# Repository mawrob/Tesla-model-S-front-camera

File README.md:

# Tesla-model-S-front-camera
Module to enable switching between a newly added front camera and the standard rear camera.

These are the camera switch manufacturing files for a Tesla Model S.

See: http://www.teslarati.com/tesla-model-s-front-camera-touchscreen-kit/

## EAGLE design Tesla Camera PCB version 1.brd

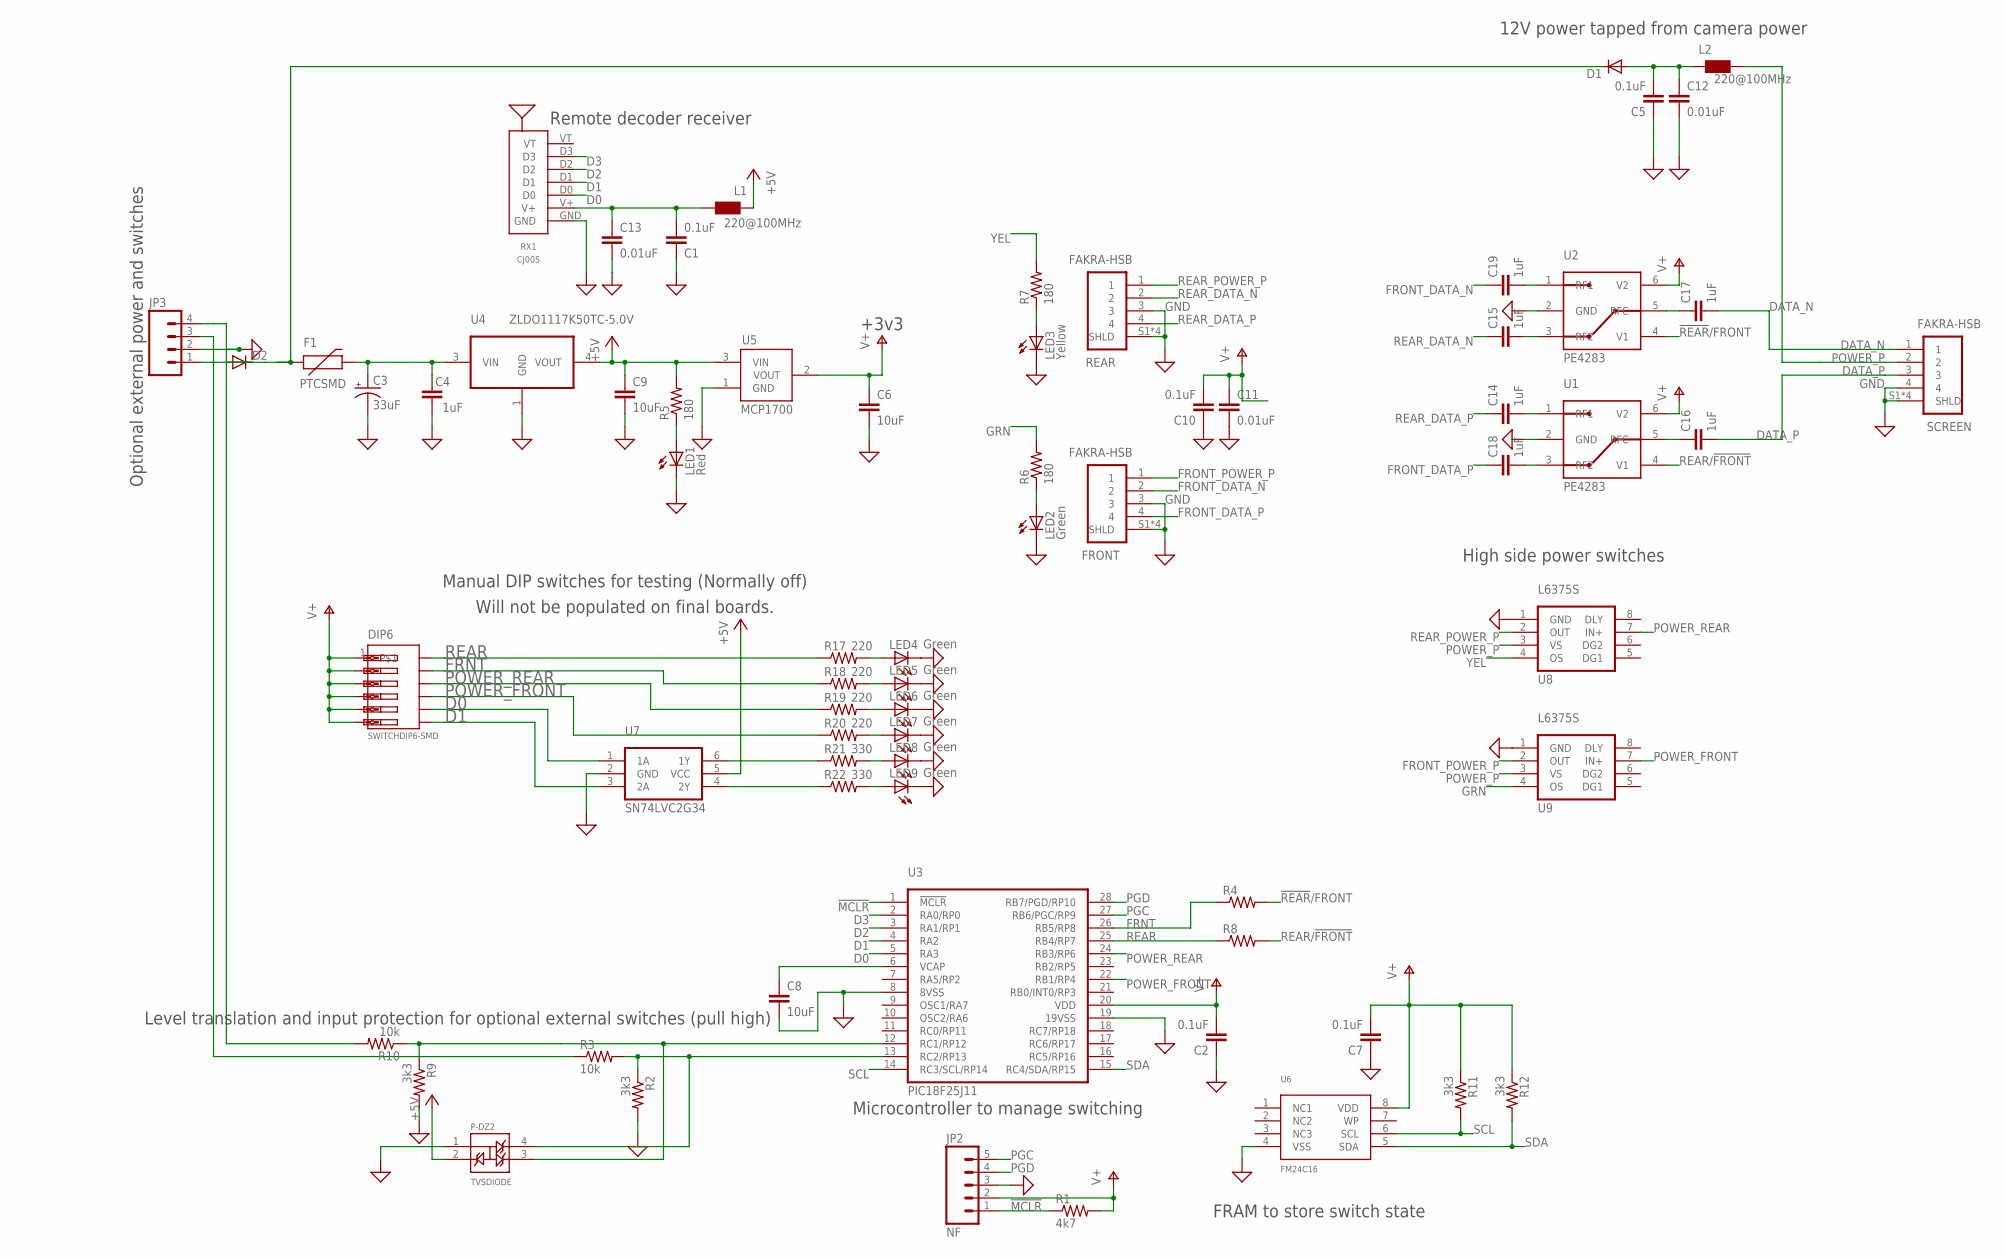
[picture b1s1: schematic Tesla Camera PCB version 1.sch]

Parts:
C1, C2, C5, C7, C10: 0.1uF; 0805
C3: 33uF; CAPVTYPE
C4: 1uF; 0805
C6, C8, C9: 10uF; 0805
C11, C12, C13: 0.01uF; 0805
C14, C15, C16, C17, C18, C19: 1uF; 0603-CAP
D1, D2: DIODE-DO-214AC; DO-214AC
DIP6: SWITCHDIP6-SMD; SWITCHDIP6
F1: PTCSMD; PTC-1206
FRONT: FAKRA-HSB; FAKRA
JP2: NF; 1X05_LOCK
JP3: M04-LOCK; 1X04_TERM_3.5MM
L1, L2: 220@100MHz; 0805
LED1: Red; 0805_LED
LED2, LED4, LED5, LED6, LED7, LED8, LED9: Green; 0805_LED
LED3: Yellow; 0805_LED
P-DZ2: TVSDIODE; SOT143
R1: 4k7; 0805
R2, R9, R11, R12: 3k3; 0805
R3, R10: 10k; 0805
R4, R8: RESISTOR; 0805
R5, R6, R7: 180; 0805
R17, R18, R19, R20: 220; 0805
R21, R22: 330; 0805
REAR: FAKRA-HSB; FAKRA
RX1: CJ005
SCREEN: FAKRA-HSB; FAKRA
U1, U2: PE4283; SC70-6
U3: PIC18F25J11; SOIC-28-WIDE
U4: ZLDO1117K50TC-5.0V; TO252
U5: MCP1700; SOT23-3
U6: FM24C16; TDFN-8-FRAM
U7: SN74LVC2G34; SOT23-6
U8, U9: L6375S; SO08-EIAJ

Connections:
!MCLR: JP2.1, R1.1, U3.1 (!MCLR)
!REAR!/FRONT: R4.2, U2.4 (V1)
+5V: C9.1, L1.1, P-DZ2.2, R5.2, U4.4 (VOUT), U5.3 (VIN), U7.5 (VCC)
D0: DIP6.8, RX1.D0, U3.5 (RA3), U7.1 (1A)
D1: DIP6.7, RX1.D1, U3.4 (RA2), U7.3 (2A)
D2: RX1.D2, U3.3 (RA1/RP1)
D3: RX1.D3, U3.2 (RA0/RP0)
DATA_N: C17.2, SCREEN.1
DATA_P: C16.2, SCREEN.3
FRNT: DIP6.11, R4.1, R18.1, U3.26 (RB5/RP8)
FRONT_DATA_N: C19.1, FRONT.2
FRONT_DATA_P: C18.1, FRONT.4
FRONT_POWER_P: FRONT.1, U9.2 (OUT)
GND: C1.1, C2.1, C3.-, C4.2, C5.1, C6.2, C7.1, C8.2, C9.2, C10.1, C11.2, C12.2, C13.2, FRONT.3, FRONT.S1 (SHLD), FRONT.S2 (SHLD), FRONT.S3 (SHLD), FRONT.S4 (SHLD), JP2.3, JP3.2, LED1.C, LED2.C, LED3.C, LED4.C, LED5.C, LED6.C, LED7.C, LED8.C, LED9.C, P-DZ2.1, R2.2, R9.2, REAR.3, REAR.S1 (SHLD), REAR.S2 (SHLD), REAR.S3 (SHLD), REAR.S4 (SHLD), RX1.GND, SCREEN.4, SCREEN.S1 (SHLD), SCREEN.S2 (SHLD), SCREEN.S3 (SHLD), SCREEN.S4 (SHLD), U1.2 (GND), U2.2 (GND), U3.8 (8VSS), U3.19 (19VSS), U4.1 (GND), U5.1 (GND), U6.4 (VSS), U7.2 (GND), U8.1 (GND), U9.1 (GND)
GRN: R6.2, U9.4 (OS)
unnamed: C5.2, C12.1, D1.A, L2.1
unnamed: P-DZ2.3, R9.1, R10.1, U3.12 (RC1/RP12)
unnamed: LED2.A, R6.1
unnamed: JP3.3, R3.1
unnamed: JP3.4, R10.2
unnamed: C8.1, U3.6 (VCAP)
unnamed: C19.2, U2.1 (RF1)
unnamed: C15.2, U2.3 (RF2)
unnamed: D1.C, D2.C, F1.1
unnamed: C17.1, U2.5 (RFC)
unnamed: D2.A, JP3.1
unnamed: C16.1, U1.5 (RFC)
unnamed: LED3.A, R7.1
unnamed: C3.+, C4.1, F1.2, U4.3 (VIN)
unnamed: LED1.A, R5.1
unnamed: C18.2, U1.3 (RF2)
unnamed: C14.2, U1.1 (RF1)
unnamed: LED4.A, R17.2
unnamed: LED5.A, R18.2
unnamed: LED6.A, R19.2
unnamed: LED7.A, R20.2
unnamed: LED8.A, R21.2
unnamed: LED9.A, R22.2
unnamed: R21.1, U7.6 (1Y)
unnamed: R22.1, U7.4 (2Y)
unnamed: P-DZ2.4, R2.1, R3.2, U3.13 (RC2/RP13)
PGC: JP2.5, U3.27 (RB6/PGC/RP9)
PGD: JP2.4, U3.28 (RB7/PGD/RP10)
POWER_FRONT: DIP6.9, R20.1, U3.22 (RB1/RP4), U9.7 (IN+)
POWER_P: L2.2, SCREEN.2, U8.3 (VS), U9.3 (VS)
POWER_REAR: DIP6.10, R19.1, U3.24 (RB3/RP6), U8.7 (IN+)
REAR: DIP6.12, R8.1, R17.1, U3.25 (RB4/RP7)
REAR/!FRONT: R8.2, U1.4 (V1)
REAR_DATA_N: C15.1, REAR.2
REAR_DATA_P: C14.1, REAR.4
REAR_POWER_P: REAR.1, U8.2 (OUT)
SCL: R11.2, U3.14 (RC3/SCL/RP14), U6.6 (SCL)
SDA: R12.2, U3.15 (RC4/SDA/RP15), U6.5 (SDA)
V+: C2.2, C6.1, C7.2, C10.2, C11.1, DIP6.1, DIP6.2, DIP6.3, DIP6.4, DIP6.5, DIP6.6, JP2.2, R1.2, R11.1, R12.1, U1.6 (V2), U2.6 (V2), U3.20 (VDD), U5.2 (VOUT), U6.8 (VDD)
V+1: C1.2, C13.1, L1.2, RX1.V+
YEL: R7.2, U8.4 (OS)

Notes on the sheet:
High side power switches
Remote decoder receiver
Optional external power and switches
FRAM to store switch state
Microcontroller to manage switching
12V power tapped from camera power
+3v3
Level translation and input protection for optional external switches (pull high)
Manual DIP switches for testing (Normally off)
Will not be populated on final boards.

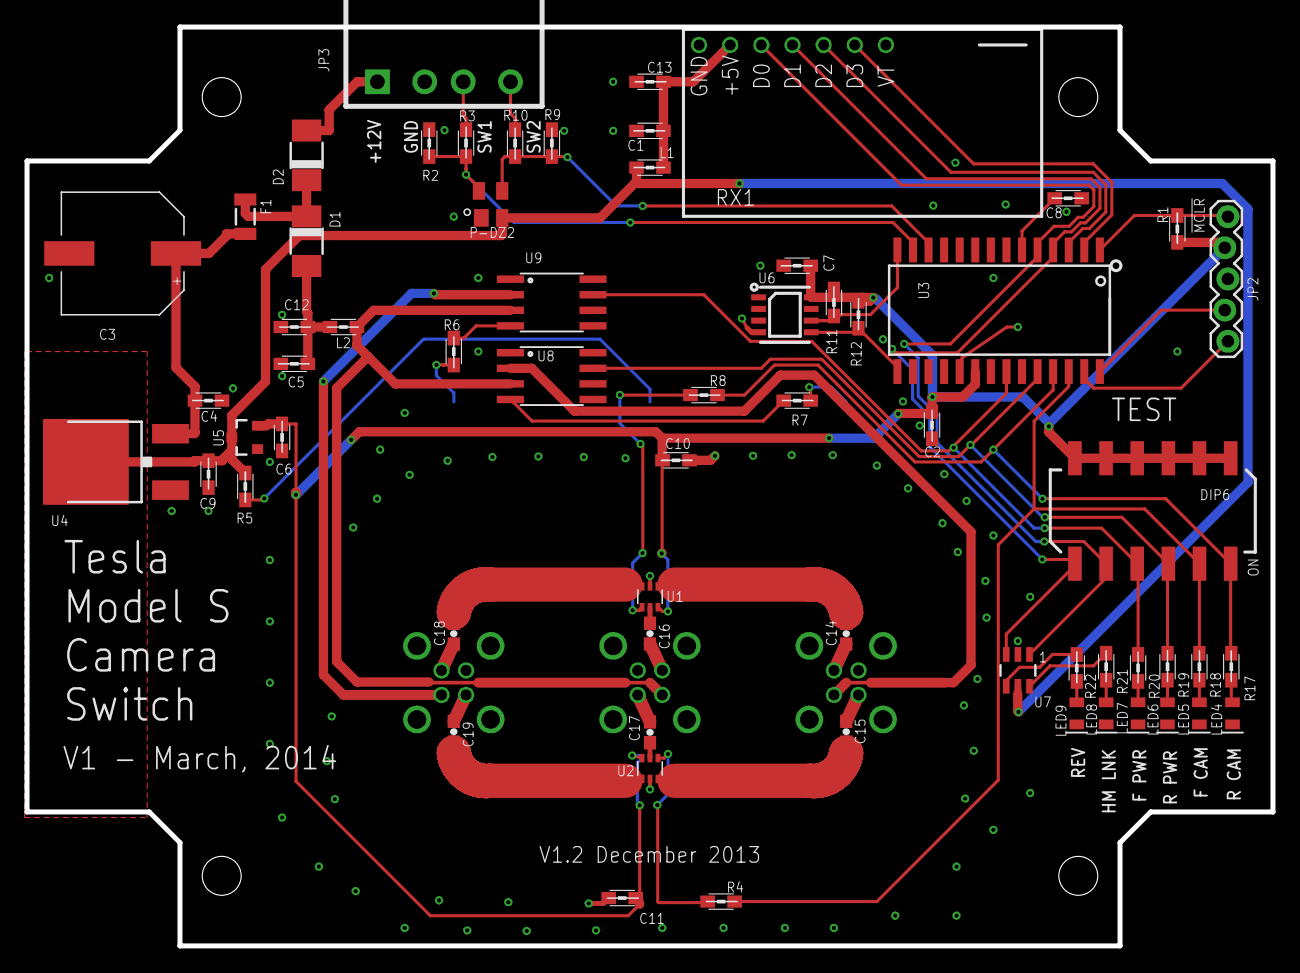
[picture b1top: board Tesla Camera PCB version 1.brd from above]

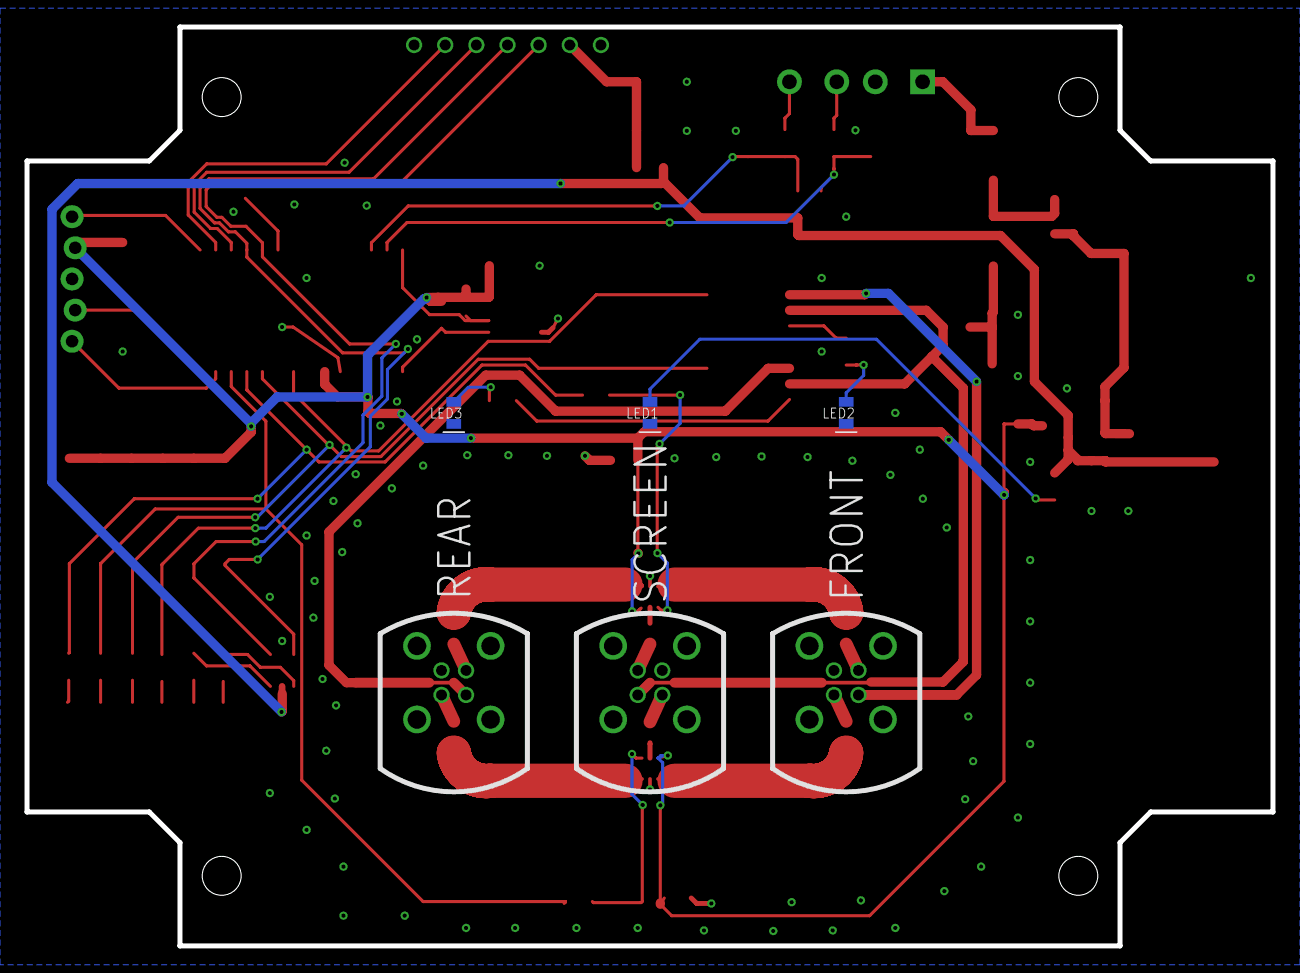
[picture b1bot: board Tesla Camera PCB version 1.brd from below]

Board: 2 copper layers, 101.6 x 74.9 mm, 68 parts (6 on the bottom side), 56 nets.

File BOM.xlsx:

VALUE | DESCRIPTION | MFR | MFPN | VEND | VPN | QTY | EACH | COST | REF | NOTES
33uF | CAP ALUM 33UF 100V 20% SMD | Nichicon | UUX2A330MNL1GS | Digi-Key | 493-6281-1-ND | 1 | 0.33428000000000002 | 0.33428000000000002 | C3 | Alternative Panasonic EEE-HD1J330P
0.1uF | CAP CER 0.1UF 50V 10% X7R 0805 | AVX CORPORATION (VA) | 08055C104KAT2A | Digi-Key | 478-1395-1-ND | 5 | 1.9E-2 | 9.5000000000000001E-2 | C10,C7,C5,C2,C1
0.01uF | CAP CER 10000PF 50V 10% X7R 0805 | Kemet | C0805C103K5RACTU | Digi-Key | 399-1158-1-ND | 3 | 1.54E-2 | 4.6200000000000005E-2 | C13,C12,C11
10uF | CAP CER 10UF 10V Y5V 0805 | Yageo | CC0805ZKY5V6BB106 | Digi-Key | 311-1355-1-ND | 3 | 5.2200000000000003E-2 | 0.15660000000000002 | C9,C8,C6
1uF | CAP CER 1UF 50V 10% X5R 0603 | Taiyo Yuden | UMK107BJ105KA-T | Digi-Key | 587-2400-1-ND | 6 | 5.2299999999999999E-2 | 0.31379999999999997 | C19,C18,C17,C16,C15,C14
1uF | CAP CER 1UF 50V Y5V 0805 | Samsung Electro-Mechanics America, Inc | CL21B105KBFNNNE | Digi-Key | 1276-1029-1-ND | 1 | 0.03 | 0.03 | C4
FAKRA-HSB | Fakra Jack PCB mount Straight 4 Contact pin Connector for Blue GPS telematics o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 |  |  | RFSupplier.com | F03-SJPT4-C | 3 | 2.73 | 8.19 | SCREEN,REAR,FRONT
220@100MHz | FERRITE CHIP 220 OHM 1500MA 0805 | Samsung Electro-Mechanics America, Inc | CIC21J221NE | Digi-Key | 1276-6372-1-ND | 2 | 2.23E-2 | 4.4600000000000001E-2 | L2,L1
SN74LVC2G34 | IC BUFFER DUAL NON-INV SOT23-6 | Texas Instruments | SN74LVC2G34DBVR | Digi-Key | 296-13496-1-ND | 1 | 0.37 | 0.37 | U7 | Do not populate
L6375S | IC DRIVER HI SIDE 0.5A IPS SOIC8 | STMicroelectronics | L6375STR | Digi-Key | 497-6865-1-ND | 2 | 2.9687999999999999 | 5.9375999999999998 | U9,U8
FM24C16 | IC FRAM 16KBIT 1MHZ 8TDFN | Cypress Semiconductor Corp | FM24CL16B-DG | Digi-Key | FM24CL16B-DGRA-ND | 1 | 1.44 | 1.44 | U6 | New 4x4.5mm footprint
PIC18F25J11 | IC MCU 8BIT 32KB FLASH 28SOIC | Microchip Technology | PIC18F25J11-I/SO | DigiKey | PIC18F25J11-I/SO-ND | 1 | 2.08 | 2.08 | U3
MCP1700 | IC REG LDO 3V 0.25A SOT23-3 | Microchip Technology | MCP1700T-3002E/TT | Digi-Key | MCP1700T-3002E/TTCT-ND | 1 | 0.28000000000000003 | 0.28000000000000003 | U5
ZLDO1117K50TC-5.0V | IC REG LDO 5V 1A TO252-3 | Diodes Incorporated | ZLDO1117K50TC | Digi-Key | ZLDO1117K50DICT-ND | 1 | 0.4017 | 0.4017 | U4
PE4283 | IC RF SWITCH SPDT 50 OHM SC70-6 | Peregrine Semiconductor | 4283-52 | Digi-Key | 1046-1030-1-ND | 2 | 0.7127 | 1.4254 | U2,U1
Green | LED 2X1.2MM 570NM GN WTR CLR SMD | Kingbright Corp | APT2012CGCK | Digi-Key | 754-1127-1-ND | 6 | 0.11 | 0.66 | LED8,LED7,LED6,LED5,LED4,LED2 | Do not populate
Green | LED 2X1.2MM 570NM GN WTR CLR SMD | Kingbright Corp | APT2012CGCK | Digi-Key | 754-1127-1-ND | 7 | 0.10730000000000001 | 0.7511000000000001 | LED9,LED8,LED7,LED6,LED5,LED4,LED2 | Do not populate
Yellow | LED 2X1.2MM 588NM YW WTR CLR SMD | Kingbright Corp | APT2012YC | Digi-Key | 754-1135-1-ND | 1 | 0.08 | 0.08 | LED3 | Do not populate
Red | LED 2X1.2MM 640NM RD WTR CLR SMD | Kingbright Corp | APT2012SRCPRV | Digi-Key | 754-1132-1-ND | 1 | 0.1 | 0.1 | LED1 | Do not populate
PTCSMD | PTC RESTTBLE 0.35A 16V CHIP 1206 | Bel Fuse Inc | 0ZCA0035FF2G | Digi-Key | 507-1479-1-ND | 1 | 1.28 | 1.28 | F1
 | RES 1.0K OHM 1/8W 5% 0805 SMD | Yageo | RC0805JR-071KL | Digi-Key | 311-1.0KARCT-ND | 2 | 7.7000000000000002E-3 | 1.54E-2 | R8,R4
10k | RES 10K OHM 1/8W 5% 0805 SMD | Yageo | RC0805JR-0710KL | Digi-Key | 311-10KARCT-ND | 2 | 7.0000000000000001E-3 | 1.4E-2 | R10,R3
180 | RES 180 OHM 1/8W 5% 0805 SMD | Yageo | RC0805JR-07180RL | Digi-Key | 311-180ARCT-ND | 3 | 7.7000000000000002E-3 | 2.3100000000000002E-2 | R7,R6,R5 | Do not populate,Do not populate,Do not populate
220 | RES 220 OHM 1/8W 5% 0805 SMD | Panasonic Electronic Components | ERJ-6GEYJ221V | Digi-Key | P220ACT-ND | 4 | 1.49E-2 | 5.96E-2 | R20,R19,R18,R17 | Do not populate,Do not populate,Do not populate,Do not populate
3k3 | RES 3.3K OHM 1/8W 5% 0805 SMD | Yageo | RC0805JR-073K3L | Digi-Key | 311-3.3KARCT-ND | 4 | 7.7000000000000002E-3 | 3.0800000000000001E-2 | R12,R11,R9,R2
330 | RES 330 OHM 1/8W 5% 0805 | Stackpole Electronics Inc | RMCF0805JT330R | Digi-Key | RMCF0805JT330RCT-ND | 2 | 7.1000000000000004E-3 | 1.4200000000000001E-2 | R22,R21 | Do not populate
4k7 | RES 4.70K OHM 1/8W 1% 0805 SMD | Yageo | RC0805FR-074K7L | Digi-Key | 311-4.70KCRCT-ND | 1 | 6.0000000000000001E-3 | 6.0000000000000001E-3 | R1
SWITCHDIP6-SMD | SWITCH DIP TOP SLIDE 6POS 24V | C&K Components | SDA06H1SBD | DigiKey | CKN6080-ND | 1 | 1.63 | 1.63 | DIP6 | Do not populate
 | TERM BLOCK HEADER 4POS R/A 3.5MM | TE Connectivity | 284512-4 | Digi-Key | A98398-ND | 1 | 2.7602000000000002 | 2.7602000000000002 | JP3 | Mates with A98375-ND $1.8952
TVSDIODE | TVS AVAL DIODE ARRAY 3 CH SOT143 | Littelfuse Inc | SP0503BAHTG | Digi-Key | F2715CT-ND | 1 | 0.51548000000000005 | 0.51548000000000005 | P-DZ2
CJ005 | Wireless Control 2 PCS 4 Way EV1527 Encoder Remotes & 1 PCS Super Regenerative 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 | Canton Electronics | RT079 | Canton Electronics | RT079 | 1 | 19.149999999999999 | 19.149999999999999 | RX1 | Plus two remotes: http://www.canton-electronics.com/wireless-control-2-pcs-4-wa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
NF |  |  |  |  |  | 0 | 0 | 0 | JP2 | Do not populate
 |  | Diodes, Inc | S1B-13-F | Digi-Key | S1B-FDITR-ND | 2 | 0.21840000000000001 | 0.43680000000000002 | D2,D1
